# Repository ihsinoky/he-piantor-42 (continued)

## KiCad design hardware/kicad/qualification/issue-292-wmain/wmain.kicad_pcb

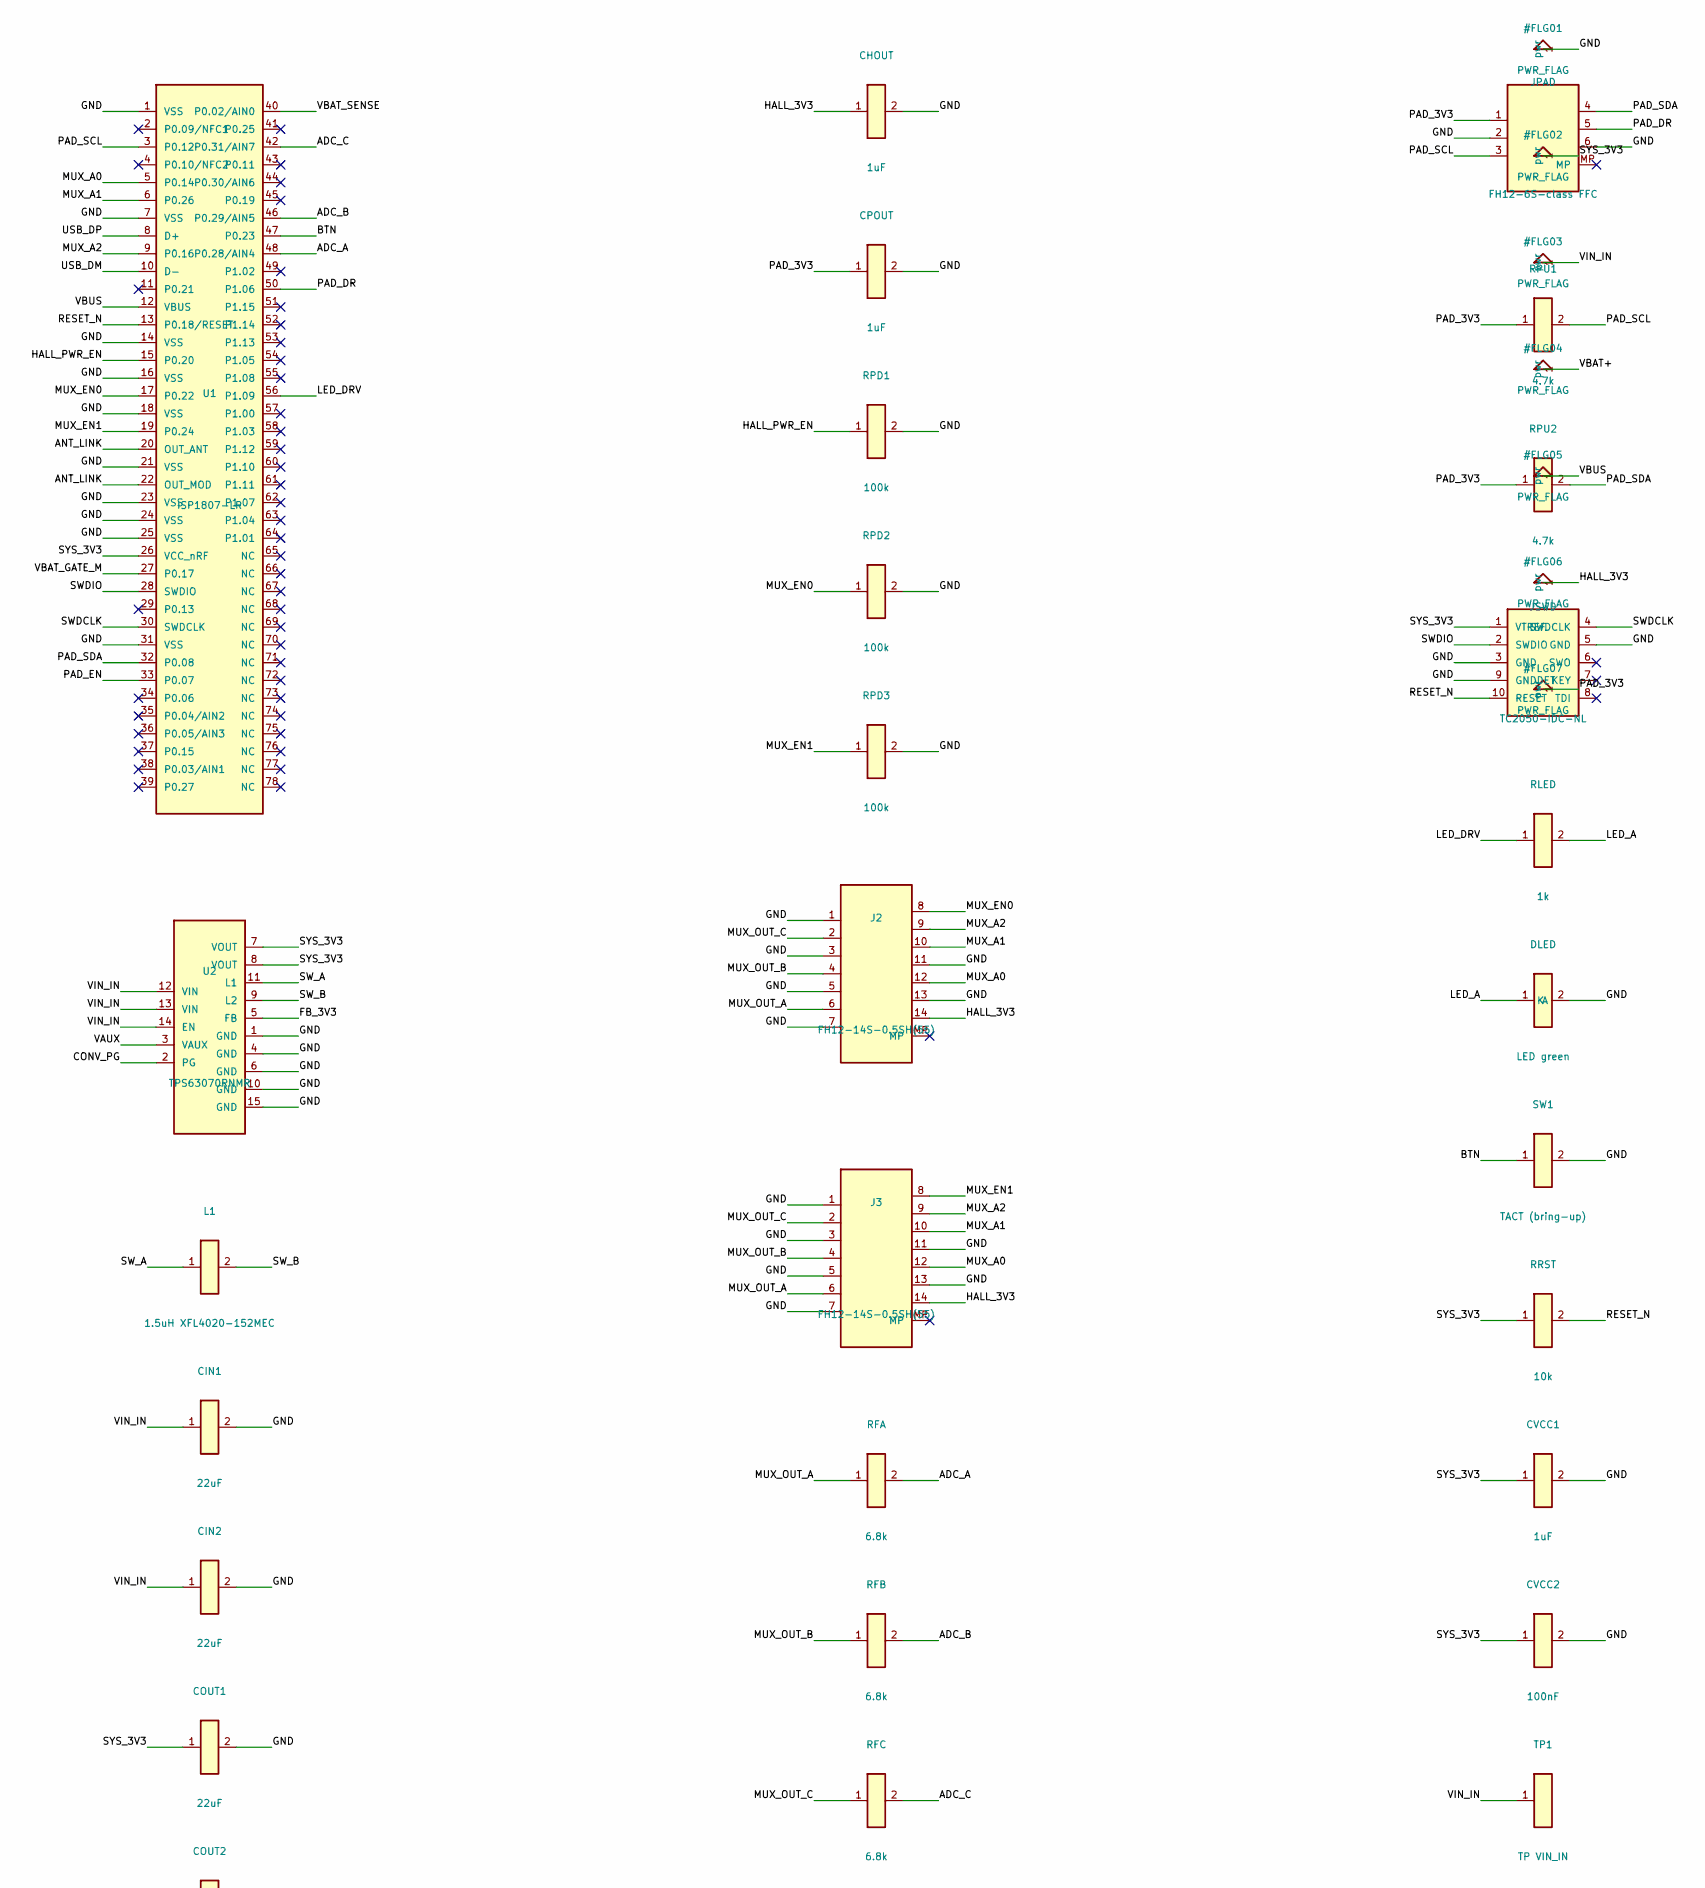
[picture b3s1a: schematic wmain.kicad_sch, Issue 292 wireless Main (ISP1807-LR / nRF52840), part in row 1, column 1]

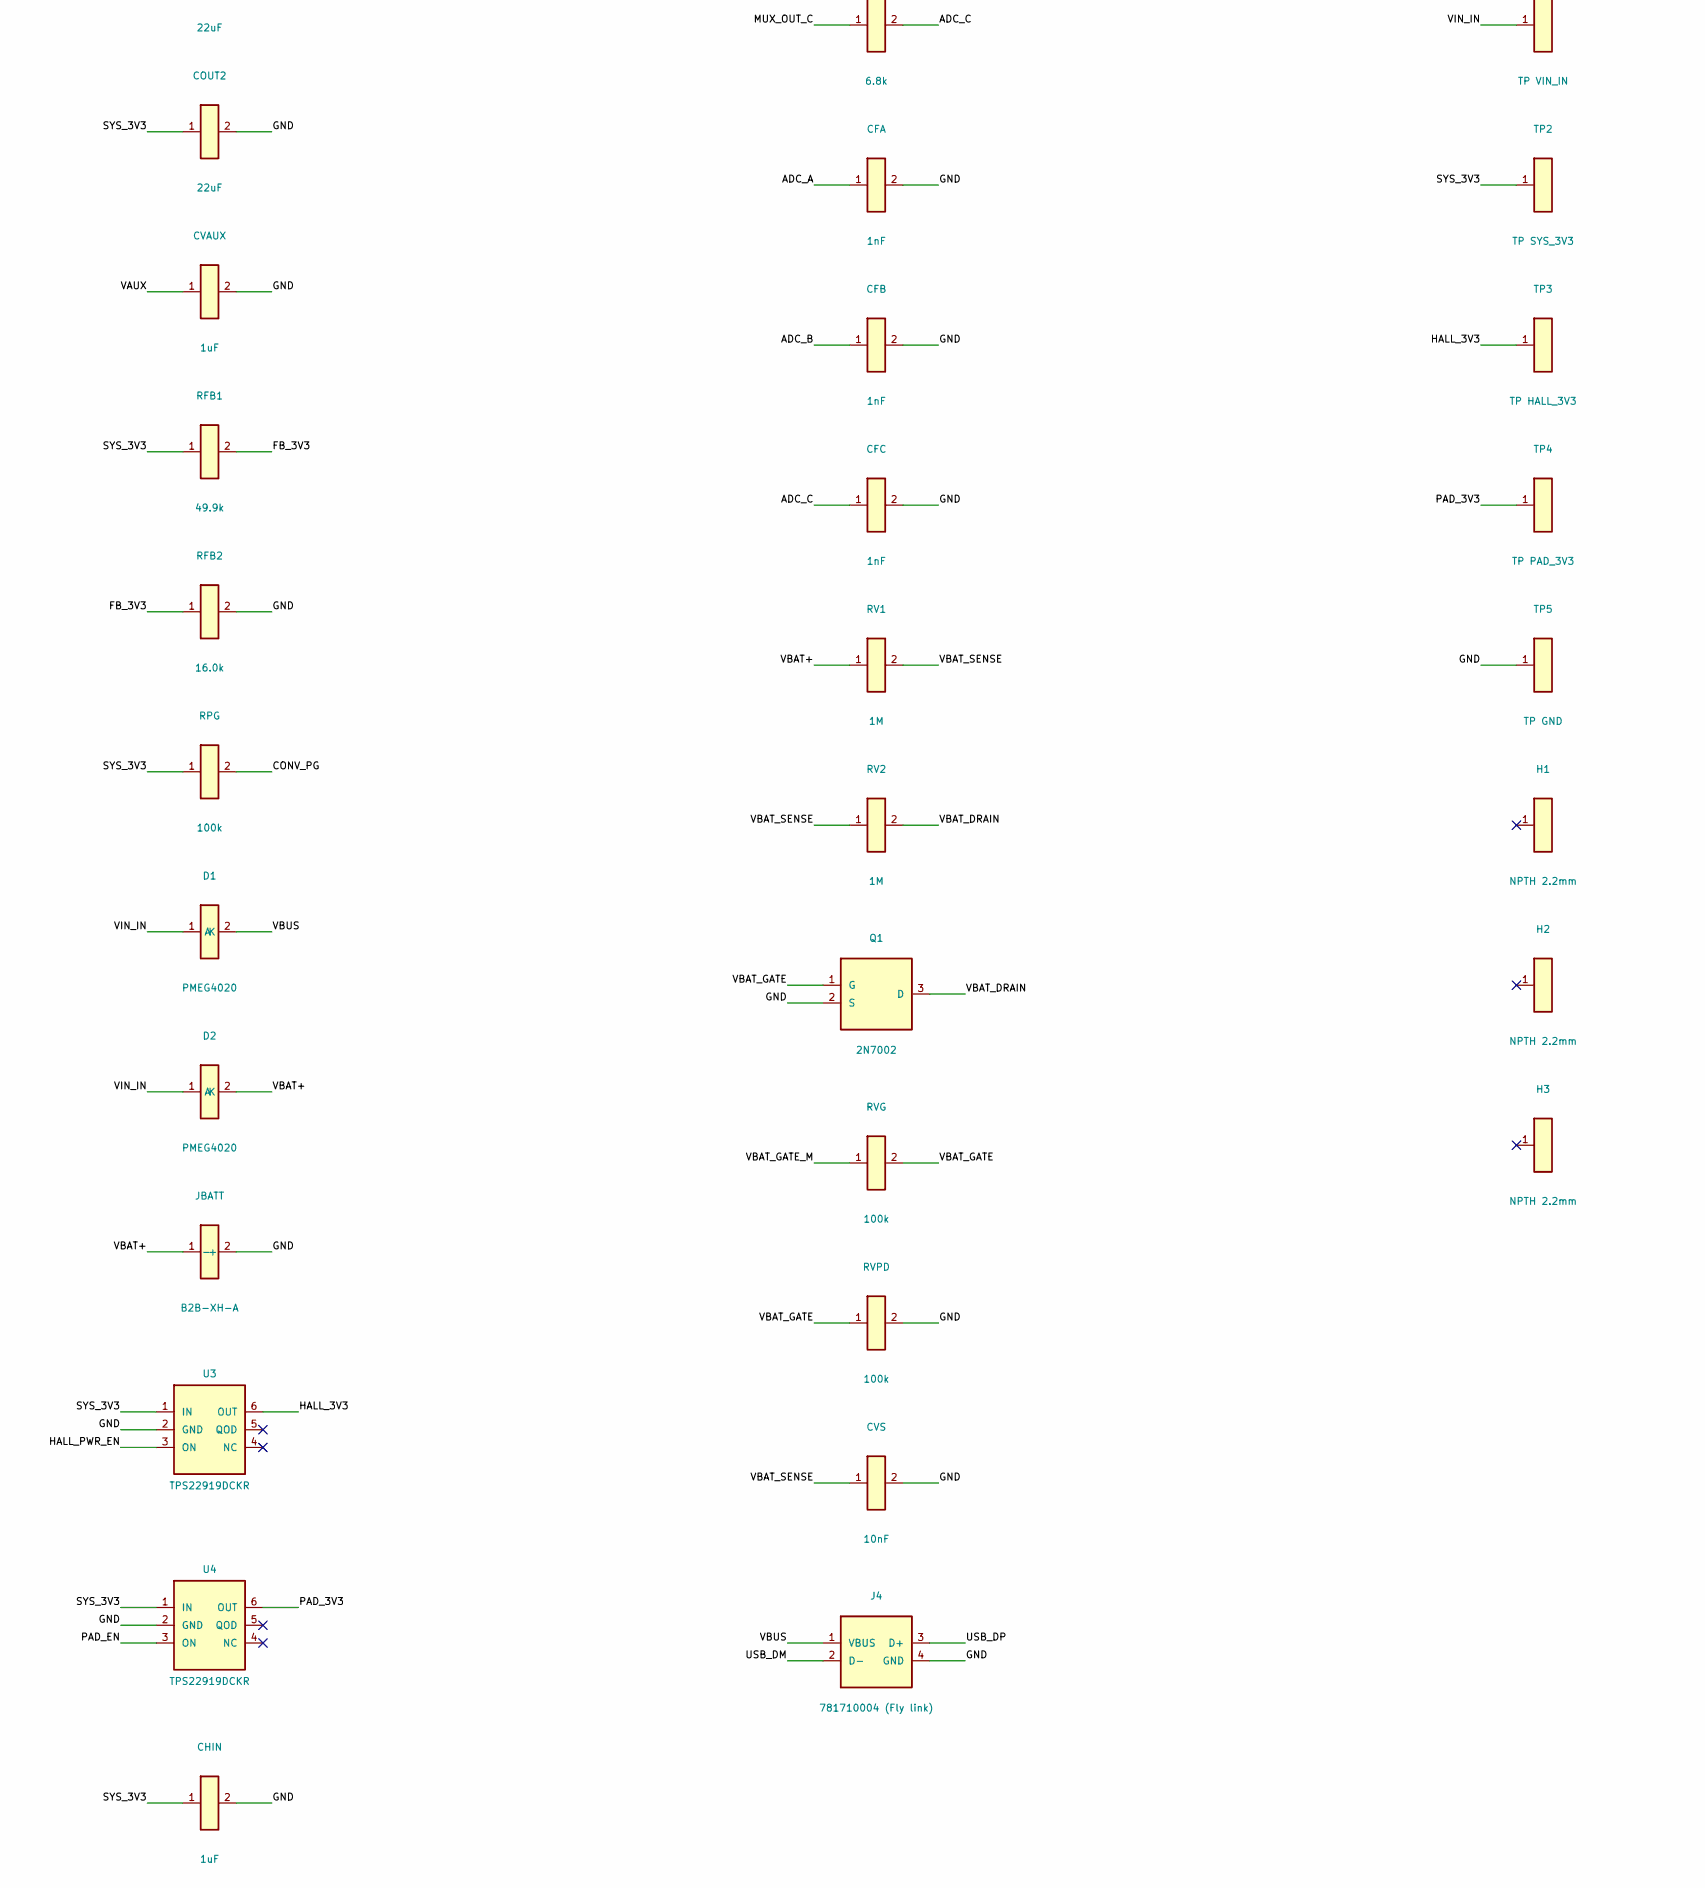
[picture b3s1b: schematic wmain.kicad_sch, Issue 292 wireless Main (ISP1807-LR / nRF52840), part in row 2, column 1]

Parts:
CFA: 1nF; C_0603
CFB: 1nF; C_0603
CFC: 1nF; C_0603
CHIN: 1uF; C_0603
CHOUT: 1uF; C_0603
CIN1, CIN2: 22uF; C_0805
COUT1, COUT2: 22uF; C_0805
CPOUT: 1uF; C_0603
CVAUX: 1uF; C_0603
CVCC1: 1uF; C_0603
CVCC2: 100nF; C_0603
CVS: 10nF; C_0603
D1, D2: PMEG4020; SOD-123
DLED: LED green; R_0603
H1, H2, H3: NPTH 2.2mm; MountingHole_2.2mm
J2, J3: FH12-14S-0.5SH(55); FH12-14S-0.5SH
J4: 781710004 (Fly link); Pico-EZmate_781710004
JBATT: B2B-XH-A; GH2
JPAD: FH12-6S-class FFC; FFC6_0.5mm_land
JSWD: TC2050-IDC-NL
L1: 1.5uH XFL4020-152MEC; XFL4020
Q1: 2N7002; SOT-23
RFA: 6.8k; R_0603
RFB: 6.8k; R_0603
RFB1: 49.9k; R_0603
RFB2: 16.0k; R_0603
RFC: 6.8k; R_0603
RLED: 1k; R_0603
RPD1, RPD2, RPD3: 100k; R_0603
RPG: 100k; R_0603
RPU1, RPU2: 4.7k; R_0603
RRST: 10k; R_0603
RV1, RV2: 1M; R_0603
RVG: 100k; R_0603
RVPD: 100k; R_0603
SW1: TACT (bring-up); TACT_2pad
TP1: TP VIN_IN; TestPoint
TP2: TP SYS_3V3; TestPoint
TP3: TP HALL_3V3; TestPoint
TP4: TP PAD_3V3; TestPoint
TP5: TP GND; TestPoint
U1: ISP1807-LR
U2: TPS63070RNMR
U3, U4: TPS22919DCKR

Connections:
ADC_A: CFA.1, RFA.2, U1.48 (P0.28/AIN4)
ADC_B: CFB.1, RFB.2, U1.46 (P0.29/AIN5)
ADC_C: CFC.1, RFC.2, U1.42 (P0.31/AIN7)
ANT_LINK: U1.20 (OUT_ANT), U1.22 (OUT_MOD)
BTN: SW1.1, U1.47 (P0.23)
CONV_PG: RPG.2, U2.2 (PG)
FB_3V3: RFB1.2, RFB2.1, U2.5 (FB)
GND: CFA.2, CFB.2, CFC.2, CHIN.2, CHOUT.2, CIN1.2, CIN2.2, COUT1.2, COUT2.2, CPOUT.2, CVAUX.2, CVCC1.2, CVCC2.2, CVS.2, DLED.2 (K), J2.1, J2.3, J2.5, J2.7, J2.11, J2.13, J3.1, J3.3, J3.5, J3.7, J3.11, J3.13, J4.4 (GND), JBATT.2 (-), JPAD.2, JPAD.6, JSWD.3 (GND), JSWD.5 (GND), JSWD.9 (GNDDET), Q1.2 (S), RFB2.2, RPD1.2, RPD2.2, RPD3.2, RVPD.2, SW1.2, TP5.1, U1.1 (VSS), U1.7 (VSS), U1.14 (VSS), U1.16 (VSS), U1.18 (VSS), U1.21 (VSS), U1.23 (VSS), U1.24 (VSS), U1.25 (VSS), U1.31 (VSS), U2.1 (GND), U2.4 (GND), U2.6 (GND), U2.10 (GND), U2.15 (GND), U3.2 (GND), U4.2 (GND)
HALL_3V3: CHOUT.1, J2.14, J3.14, TP3.1, U3.6 (OUT)
HALL_PWR_EN: RPD1.1, U1.15 (P0.20), U3.3 (ON)
LED_A: DLED.1 (A), RLED.2
LED_DRV: RLED.1, U1.56 (P1.09)
MUX_A0: J2.12, J3.12, U1.5 (P0.14)
MUX_A1: J2.10, J3.10, U1.6 (P0.26)
MUX_A2: J2.9, J3.9, U1.9 (P0.16)
MUX_EN0: J2.8, RPD2.1, U1.17 (P0.22)
MUX_EN1: J3.8, RPD3.1, U1.19 (P0.24)
MUX_OUT_A: J2.6, J3.6, RFA.1
MUX_OUT_B: J2.4, J3.4, RFB.1
MUX_OUT_C: J2.2, J3.2, RFC.1
PAD_3V3: CPOUT.1, JPAD.1, RPU1.1, RPU2.1, TP4.1, U4.6 (OUT)
PAD_DR: JPAD.5, U1.50 (P1.06)
PAD_EN: U1.33 (P0.07), U4.3 (ON)
PAD_SCL: JPAD.3, RPU1.2, U1.3 (P0.12)
PAD_SDA: JPAD.4, RPU2.2, U1.32 (P0.08)
RESET_N: JSWD.10 (RESET), RRST.2, U1.13 (P0.18/RESET)
SWDCLK: JSWD.4 (SWDCLK), U1.30 (SWDCLK)
SWDIO: JSWD.2 (SWDIO), U1.28 (SWDIO)
SW_A: L1.1, U2.11 (L1)
SW_B: L1.2, U2.9 (L2)
SYS_3V3: CHIN.1, COUT1.1, COUT2.1, CVCC1.1, CVCC2.1, JSWD.1 (VTREF), RFB1.1, RPG.1, RRST.1, TP2.1, U1.26 (VCC_nRF), U2.7 (VOUT), U2.8 (VOUT), U3.1 (IN), U4.1 (IN)
USB_DM: J4.2 (D-), U1.10 (D-)
USB_DP: J4.3 (D+), U1.8 (D+)
VAUX: CVAUX.1, U2.3 (VAUX)
VBAT+: D2.2 (A), JBATT.1 (+), RV1.1
VBAT_DRAIN: Q1.3 (D), RV2.2
VBAT_GATE: Q1.1 (G), RVG.2, RVPD.1
VBAT_GATE_M: RVG.1, U1.27 (P0.17)
VBAT_SENSE: CVS.1, RV1.2, RV2.1, U1.40 (P0.02/AIN0)
VBUS: D1.2 (A), J4.1 (VBUS), U1.12 (VBUS)
VIN_IN: CIN1.1, CIN2.1, D1.1 (K), D2.1 (K), TP1.1, U2.12 (VIN), U2.13 (VIN), U2.14 (EN)

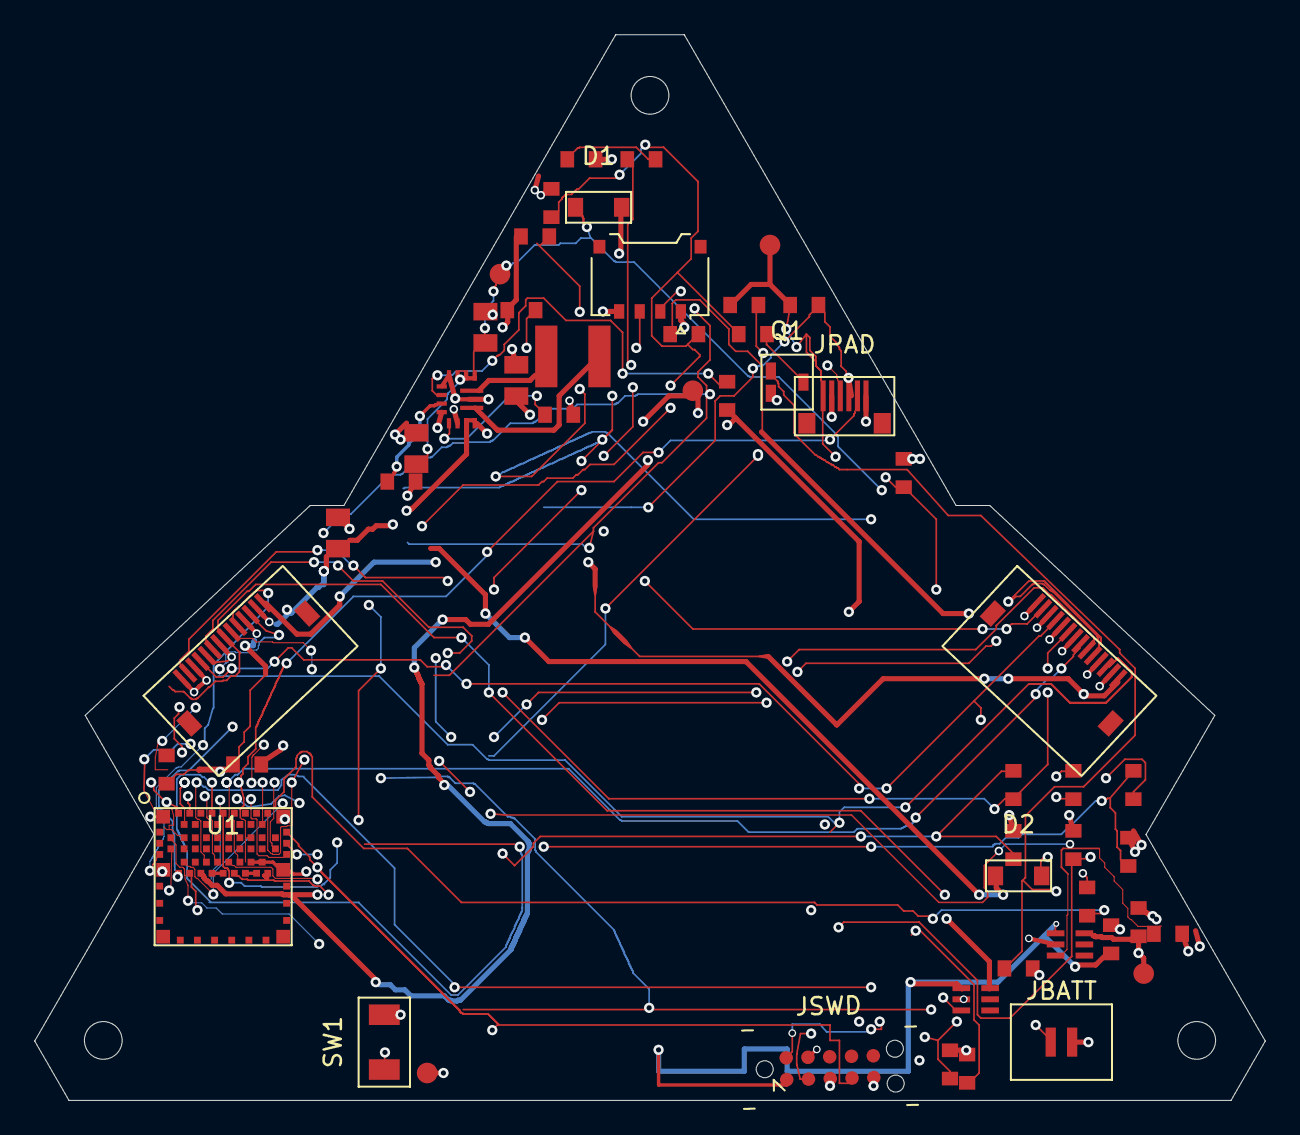
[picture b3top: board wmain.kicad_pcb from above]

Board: 4 copper layers, 71.8 x 62.2 mm, 55 parts (0 on the bottom side), 41 nets.

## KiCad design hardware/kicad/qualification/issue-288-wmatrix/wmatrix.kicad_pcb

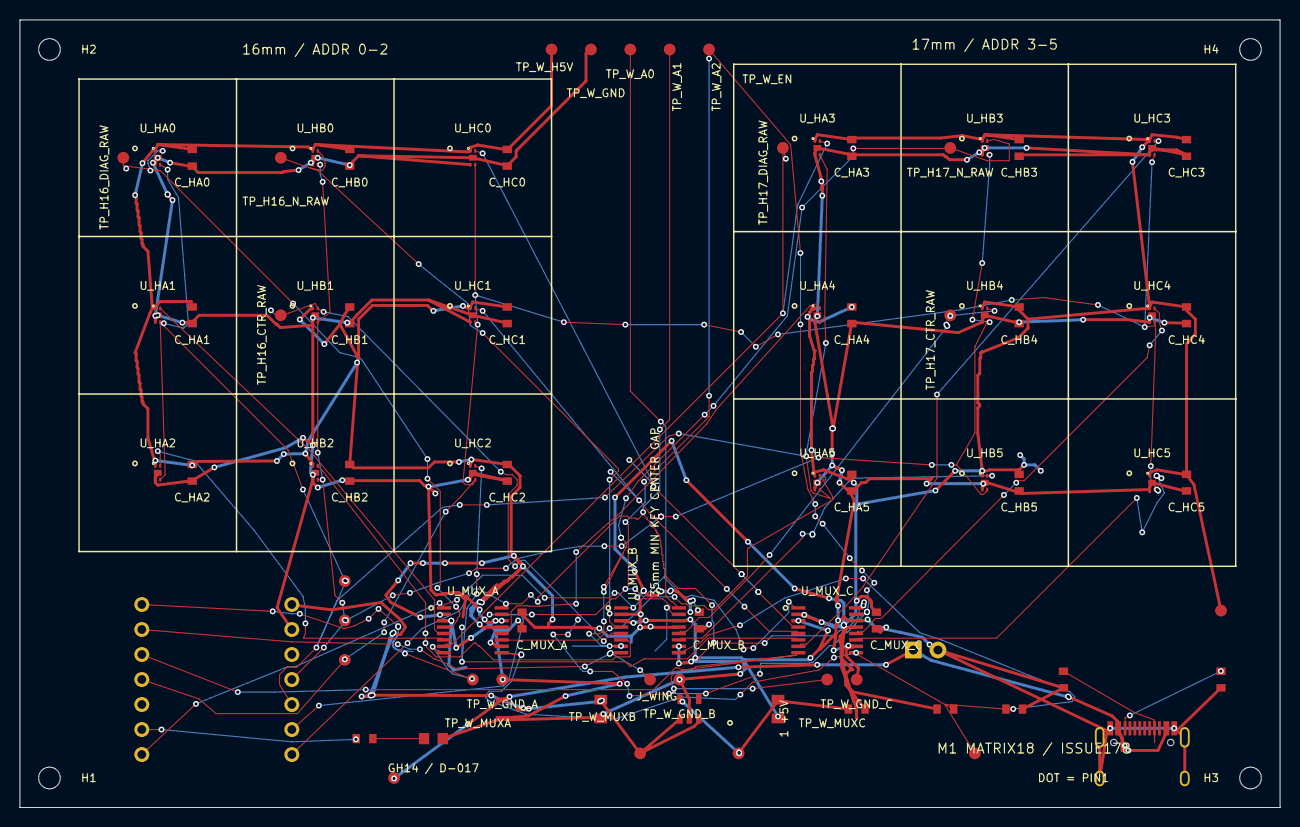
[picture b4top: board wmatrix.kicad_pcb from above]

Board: 2 copper layers, 128.0 x 80.0 mm, 85 parts (0 on the bottom side), 37 nets.

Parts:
C_HA0, C_HA1, C_HA2, C_HA3, C_HA4, C_HA5: GRM188R71C104KA01D; capacitor
C_HB0, C_HB1, C_HB2, C_HB3, C_HB4, C_HB5: GRM188R71C104KA01D; capacitor
C_HC0, C_HC1, C_HC2, C_HC3, C_HC4, C_HC5: GRM188R71C104KA01D; capacitor
C_LDO_IN: 10uF; C_0805
C_LDO_OUT: 10uF; C_0805
C_MUX_A: GRM188R71C104KA01D; capacitor
C_MUX_B: GRM188R71C104KA01D; capacitor
C_MUX_C: GRM188R71C104KA01D; capacitor
D_LED: KT-0805G green; LED_0805
H1, H2, H3, H4: NPTH_2.2mm; mounting
J_BATT: B2B-XH-A; JST_XH_B2B-XH-A_1x02
J_USB: TYPE-C-31-M-12
Q_PROT: AO3401A; AO3401A_SOT-23
R_CC1, R_CC2: 5.1k; R_0603
R_DIV1, R_DIV2: 10k; R_0603
R_LED: 1k; R_0603
R_SHUNT: 0R (current-shunt position); R_0603
TP_3V3_SRC: TestPoint; TP_1.2mm
TP_A0, TP_A1, TP_A2: PCB_PAD_1.2MM; testpoint
TP_EN_A: TestPoint; TP_1.2mm
TP_EN_B: TestPoint; TP_1.2mm
TP_EN_C: TestPoint; TP_1.2mm
TP_GND_A: PCB_PAD_1.2MM; testpoint
TP_GND_B: PCB_PAD_1.2MM; testpoint
TP_GND_C: PCB_PAD_1.2MM; testpoint
TP_GND_D: PCB_PAD_1.2MM; testpoint
TP_H16_CTR, TP_H16_DIAG, TP_H16_N, TP_H17_CTR, TP_H17_DIAG, TP_H17_N: PCB_PAD_1.2MM; testpoint
TP_MUXA: PCB_PAD_1.2MM; testpoint
TP_MUXB: PCB_PAD_1.2MM; testpoint
TP_MUXC: PCB_PAD_1.2MM; testpoint
TP_RAIL_E: TestPoint; TP_1.2mm
TP_RAIL_N: PCB_PAD_1.2MM; testpoint
TP_REF: TestPoint; TP_1.2mm
TP_VIN: TestPoint; TP_1.2mm
TP_VIN_SRC: TestPoint; TP_1.2mm
U_HA0, U_HA1, U_HA2, U_HA3, U_HA4, U_HA5: TMAG5253BA3IQDMRR; TMAG5253BA3_X2SON-4
U_HB0, U_HB1, U_HB2, U_HB3, U_HB4, U_HB5: TMAG5253BA3IQDMRR; TMAG5253BA3_X2SON-4
U_HC0, U_HC1, U_HC2, U_HC3, U_HC4, U_HC5: TMAG5253BA3IQDMRR; TMAG5253BA3_X2SON-4
U_LDO: AP2112K-3.3TRG1; AP2112_SOT-23-5
U_MUXA: TMUX1208PWR; mux
U_MUXB: TMUX1208PWR; mux
U_MUXC: TMUX1208PWR; mux
U_XIAO: XIAO nRF52840 (socket, hand-fit); XIAO_nRF52840_SOCKET

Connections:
CC1: J_USB.3, R_CC1.1
CC2: J_USB.10, R_CC2.1
EN_A: TP_EN_A.1, U_HA0.3, U_HA1.3, U_HA2.3, U_HA3.3, U_HA4.3, U_HA5.3, U_XIAO.10
EN_B: TP_EN_B.1, U_HB0.3, U_HB1.3, U_HB2.3, U_HB3.3, U_HB4.3, U_HB5.3, U_XIAO.11
EN_C: TP_EN_C.1, U_HC0.3, U_HC1.3, U_HC2.3, U_HC3.3, U_HC4.3, U_HC5.3, U_XIAO.4
GND: C_HA0.2, C_HA1.2, C_HA2.2, C_HA3.2, C_HA4.2, C_HA5.2, C_HB0.2, C_HB1.2, C_HB2.2, C_HB3.2, C_HB4.2, C_HB5.2, C_HC0.2, C_HC1.2, C_HC2.2, C_HC3.2, C_HC4.2, C_HC5.2, C_LDO_IN.2, C_LDO_OUT.2, C_MUX_A.2, C_MUX_B.2, C_MUX_C.2, D_LED.2, J_BATT.2, J_USB.1, J_USB.12, J_USB.13, Q_PROT.1, R_CC1.2, R_CC2.2, R_DIV2.2, TP_GND_A.1, TP_GND_B.1, TP_GND_C.1, TP_GND_D.1, U_HA0.2, U_HA0.5, U_HA1.2, U_HA1.5, U_HA2.2, U_HA2.5, U_HA3.2, U_HA3.5, U_HA4.2, U_HA4.5, U_HA5.2, U_HA5.5, U_HB0.2, U_HB0.5, U_HB1.2, U_HB1.5, U_HB2.2, U_HB2.5, U_HB3.2, U_HB3.5, U_HB4.2, U_HB4.5, U_HB5.2, U_HB5.5, U_HC0.2, U_HC0.5, U_HC1.2, U_HC1.5, U_HC2.2, U_HC2.5, U_HC3.2, U_HC3.5, U_HC4.2, U_HC4.5, U_HC5.2, U_HC5.5, U_LDO.2, U_MUXA.3, U_MUXA.10, U_MUXA.14, U_MUXB.3, U_MUXB.10, U_MUXB.14, U_MUXC.3, U_MUXC.10, U_MUXC.14, U_XIAO.13
HALL_3V3: C_HA0.1, C_HA1.1, C_HA2.1, C_HA3.1, C_HA4.1, C_HA5.1, C_HB0.1, C_HB1.1, C_HB2.1, C_HB3.1, C_HB4.1, C_HB5.1, C_HC0.1, C_HC1.1, C_HC2.1, C_HC3.1, C_HC4.1, C_HC5.1, C_MUX_A.1, C_MUX_B.1, C_MUX_C.1, R_DIV1.1, R_SHUNT.2, TP_RAIL_E.1, TP_RAIL_N.1, U_HA0.1, U_HA1.1, U_HA2.1, U_HA3.1, U_HA4.1, U_HA5.1, U_HB0.1, U_HB1.1, U_HB2.1, U_HB3.1, U_HB4.1, U_HB5.1, U_HC0.1, U_HC1.1, U_HC2.1, U_HC3.1, U_HC4.1, U_HC5.1, U_MUXA.2, U_MUXA.13, U_MUXB.2, U_MUXB.13, U_MUXC.2, U_MUXC.13
HALL_3V3_SRC: C_LDO_OUT.1, R_SHUNT.1, TP_3V3_SRC.1, U_LDO.5
H_A0_RAW: TP_H16_DIAG.1, U_HA0.4, U_MUXA.4
H_A1_RAW: U_HA1.4, U_MUXA.5
H_A2_RAW: U_HA2.4, U_MUXA.6
H_A3_RAW: TP_H17_DIAG.1, U_HA3.4, U_MUXA.7
H_A4_RAW: U_HA4.4, U_MUXA.12
H_A5_RAW: U_HA5.4, U_MUXA.11
H_B0_RAW: TP_H16_N.1, U_HB0.4, U_MUXB.4
H_B1_RAW: TP_H16_CTR.1, U_HB1.4, U_MUXB.5
H_B2_RAW: U_HB2.4, U_MUXB.6
H_B3_RAW: TP_H17_N.1, U_HB3.4, U_MUXB.7
H_B4_RAW: TP_H17_CTR.1, U_HB4.4, U_MUXB.12
H_B5_RAW: U_HB5.4, U_MUXB.11
H_C0_RAW: U_HC0.4, U_MUXC.4
H_C1_RAW: U_HC1.4, U_MUXC.5
H_C2_RAW: U_HC2.4, U_MUXC.6
H_C3_RAW: U_HC3.4, U_MUXC.7
H_C4_RAW: U_HC4.4, U_MUXC.12
H_C5_RAW: U_HC5.4, U_MUXC.11
LED_A: D_LED.1, R_LED.2
LED_DRV: R_LED.1, U_XIAO.6
MUXA_OUT: TP_MUXA.1, U_MUXA.8, U_XIAO.1
MUXB_OUT: TP_MUXB.1, U_MUXB.8, U_XIAO.2
MUXC_OUT: TP_MUXC.1, U_MUXC.8, U_XIAO.3
MUX_A0: TP_A0.1, U_MUXA.1, U_MUXB.1, U_MUXC.1, U_XIAO.7
MUX_A1: TP_A1.1, U_MUXA.16, U_MUXB.16, U_MUXC.16, U_XIAO.8
MUX_A2: TP_A2.1, U_MUXA.15, U_MUXB.15, U_MUXC.15, U_XIAO.9
REF_RAIL: R_DIV1.2, R_DIV2.1, TP_REF.1, U_MUXA.9, U_MUXB.9, U_MUXC.9
VIN: C_LDO_IN.1, Q_PROT.3, TP_VIN.1, U_LDO.1, U_LDO.3, U_XIAO.14
VIN_SRC: J_BATT.1, J_USB.2, J_USB.11, Q_PROT.2, TP_VIN_SRC.1

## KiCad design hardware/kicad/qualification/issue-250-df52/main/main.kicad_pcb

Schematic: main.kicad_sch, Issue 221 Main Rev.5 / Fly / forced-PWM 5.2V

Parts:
C1: 15pF; C1
C2: 15pF; C2
C3: 100nF; C3
C4: 100nF; C4
C5: 100nF; C5
C6: 100nF; C6
C7: 100nF; C7
C8: 100nF; C8
C9: 100nF; C9
C10: 100nF; C10
C11: 100nF; C11
C12: 1uF; C12
C13: 1uF; C13
C14: 10uF; C14
C15: 100nF; C15
C16: 1uF; C16
C17: 1uF; C17
C18: 1uF; C18
C19: 1uF; C19
C20: 1nF; C20
C21: 1nF; C21
C22: 1nF; C22
C23: 22uF 16V X6S 0805; C23
C24: 22uF 16V X6S 0805; C24
C25: 100nF; C25
C26: 22uF 16V X7R 1210; C26
C27: 22uF 16V X7R 1210; C27
C28: 22uF 16V X7R 1210; C28
H1: NPTH_2.2mm; H1
H2: NPTH_2.2mm; H2
H3: NPTH_2.2mm; H3
J2, J3: DF52-14S-0.8H(21); DF52-14S-0.8H_14
J4: 781710004; J4
L1: 1.5uH XFL4020-152MEC; L1
R3: 27; R3
R4: 27; R4
R5: 1k; R5
R6: 100k; R6
R7: 100k; R7
R8: 10k; R8
R9: 1k; R9
R10: 6.8k; R10
R11: 10k; R11
R12: 6.8k; R12
R13: 10k; R13
R14: 6.8k; R14
R15: 10k; R15
R16: 100k; R16
R17: 54.9k 0.1% 25ppm/K; R17
R18: 10k 0.1% 25ppm/K; R18
R19: 100k; R19
TP1: TestPoint; TP1
TP2: TestPoint; TP2
TP3: TestPoint; TP3
TP4: TestPoint; TP4
U1: RP2040; U1
U3: W25Q16JVUXIQ; U3
U4: AP2112K-3.3TRG1; U4
U5: TPS22919DCKR; U5
U6: TPS63070RNMR; U6
Y1: ABM8-272-T3; Y1

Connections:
ADC_A: C20.1, R10.2, R11.1, U1.38 (GPIO26/ADC0)
ADC_B: C21.1, R12.2, R13.1, U1.39 (GPIO27/ADC1)
ADC_C: C22.1, R14.2, R15.1, U1.40 (GPIO28/ADC2)
FB_5V2: R17.2, R18.1, U6.5 (FB)
GND: C1.2, C2.2, C3.2, C4.2, C5.2, C6.2, C7.2, C8.2, C9.2, C10.2, C11.2, C12.2, C13.2, C14.2, C15.2, C16.2, C17.2, C18.2, C19.2, C20.2, C21.2, C22.2, C23.2, C24.2, C25.2, C26.2, C27.2, C28.2, J2.2, J2.4, J2.8, J2.10, J2.12, J2.14, J3.2, J3.4, J3.8, J3.10, J3.12, J3.14, J4.4, R6.2, R7.2, R11.2, R13.2, R15.2, R16.2, R18.2, U1.19 (TESTEN), U1.57 (GND), U3.4 (GND), U4.2 (GND), U5.2 (GND), U6.1 (PS/SYNC), U6.4 (GND), U6.6 (FB2), U6.10 (PGND), U6.15 (VSEL), Y1.2 (G), Y1.4 (G)
HALL_5V: C19.1, J2.1, J3.1, U5.6 (OUT)
HALL_PWR_EN: R7.1, U1.9 (GPIO7), U5.3 (ON), U6.14 (EN)
MUX_A0: J2.3, J3.3, U1.4 (GPIO2)
MUX_A1: J2.5, J3.5, U1.5 (GPIO3)
MUX_A2: J2.6, J3.6, U1.6 (GPIO4)
MUX_EN1: J3.7, R16.1, U1.8 (GPIO6)
MUX_OUT_A: J2.9, J3.9, R10.1
MUX_OUT_B: J2.11, J3.11, R12.1
MUX_OUT_C: J2.13, J3.13, R14.1
QSPI_SCLK: U1.52 (QSPI_SCLK), U3.6 (CLK)
QSPI_SD0: U1.53 (QSPI_SD0), U3.5 (DI(IO0))
QSPI_SD1: U1.55 (QSPI_SD1), U3.2 (DO(IO1))
QSPI_SD2: U1.54 (QSPI_SD2), U3.3 (~WP(IO2))
QSPI_SD3: U1.51 (QSPI_SD3), U3.7 (~HOLD(IO3))
QSPI_SS_FLASH: R5.2, TP4.1, U3.1 (~CS)
QSPI_SS_MCU: R5.1, U1.56 (~QSPI_SS)
RAIL_PG: R19.2, U6.2 (PG)
RUN: R8.2, TP3.1, U1.26 (RUN)
SW1: L1.1, U6.11 (L1)
SW2: L1.2, U6.9 (L2)
SWCLK: TP2.1, U1.24 (SWCLK)
SWDIO: TP1.1, U1.25 (SWDIO)
USB_DM: R4.2, U1.46 (USB_DM)
USB_DM_ESD: J4.2, R4.1
USB_DP: R3.2, U1.47 (USB_DP)
USB_DP_ESD: J4.3, R3.1
V1V1: C11.1, C13.1, U1.23 (DVDD), U1.45 (VREG_VOUT), U1.50 (DVDD)
V3V3: C3.1, C4.1, C5.1, C6.1, C7.1, C8.1, C9.1, C10.1, C12.1, C14.1, C15.1, C17.1, R8.1, R19.1, U1.1 (IOVDD), U1.10 (IOVDD), U1.22 (IOVDD), U1.33 (IOVDD), U1.42 (IOVDD), U1.43 (ADC_AVDD), U1.44 (VREG_VIN), U1.48 (USB_VDD), U1.49 (IOVDD), U3.8 (VCC), U4.5 (VOUT)
V5V2: C26.1, C27.1, C28.1, R17.1, U5.1 (IN), U6.7 (VOUT), U6.8 (VOUT)
VAUX: C25.1, U6.3 (VAUX)
VBUS: C16.1, C18.1, C23.1, C24.1, J4.1, U4.1 (VIN), U4.3 (EN), U6.12 (VIN), U6.13 (VIN)
WING_EN: J2.7, R6.1, U1.7 (GPIO5)
XIN: C1.1, U1.20 (XIN), Y1.1
XOUT: R9.2, U1.21 (XOUT)
XOUT_XTAL: C2.1, R9.1, Y1.3

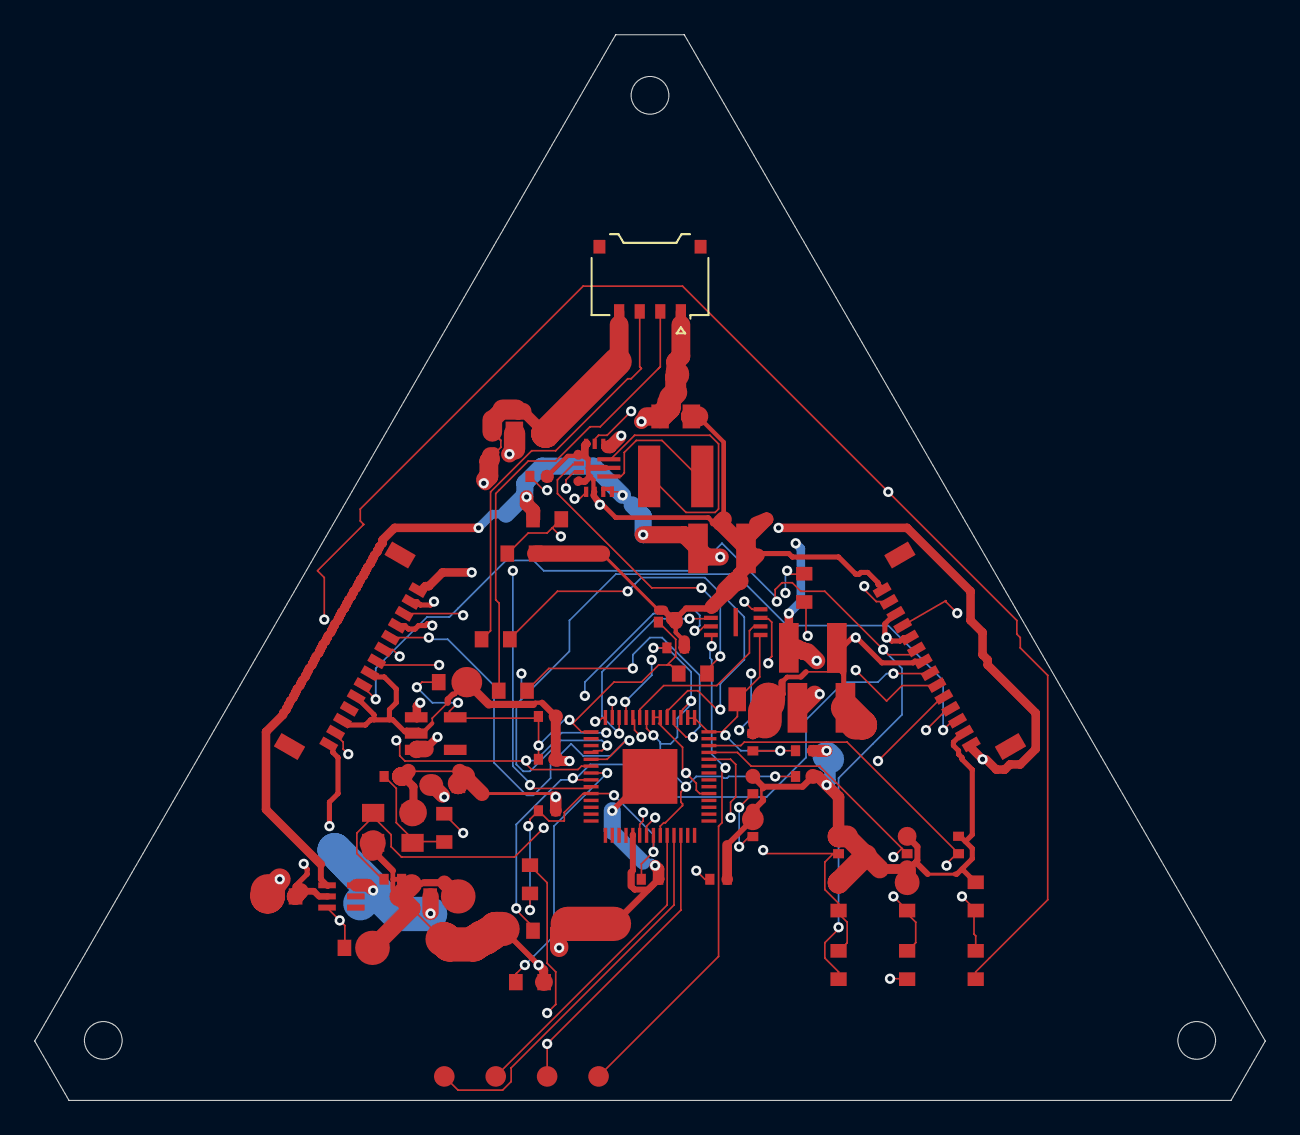
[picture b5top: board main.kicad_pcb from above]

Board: 4 copper layers, 71.8 x 62.2 mm, 62 parts (0 on the bottom side), 40 nets.

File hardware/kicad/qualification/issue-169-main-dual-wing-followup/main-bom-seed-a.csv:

ref,value,footprint,part_number,lcsc,assembled,source,procurement_confirmed
C1,15pF,Stage169:C1,0402CG150J500NT,C1548,True,Inherited #124 ledger,False
C10,100nF,Stage169:C10,CL05B104KO5NNNC,C1525,True,Inherited #124 ledger,False
C11,100nF,Stage169:C11,CL05B104KO5NNNC,C1525,True,Inherited #124 ledger,False
C12,1uF,Stage169:C12,CL05A105KA5NQNC,C52923,True,Inherited #124 ledger,False
C13,1uF,Stage169:C13,CL05A105KA5NQNC,C52923,True,Inherited #124 ledger,False
C14,10uF,Stage169:C14,CL21A106KAYNNNE,C15850,True,Inherited #124 ledger,False
C15,100nF,Stage169:C15,CL05B104KO5NNNC,C1525,True,Inherited #124 ledger,False
C16,1uF,Stage169:C16,CL10A105KB8NNNC,C15849,True,Inherited #124 ledger,False
C17,1uF,Stage169:C17,CL10A105KB8NNNC,C15849,True,Inherited #124 ledger,False
C18,1uF,Stage169:C18,CL10A105KB8NNNC,C15849,True,Inherited #124 ledger,False
C19,1uF,Stage169:C19,CL10A105KB8NNNC,C15849,True,Inherited #124 ledger,False
C2,15pF,Stage169:C2,0402CG150J500NT,C1548,True,Inherited #124 ledger,False
C20,1nF,Stage169:C20,0402B102K500NT,C1523,True,Inherited #124 ledger,False
C21,1nF,Stage169:C21,0402B102K500NT,C1523,True,Inherited #124 ledger,False
C22,1nF,Stage169:C22,0402B102K500NT,C1523,True,Inherited #124 ledger,False
C23,22uF 16V X6S 0805,Stage169:C23,GRM21BC81C226ME44L,C258782,True,Issue169 selected exact MPN; sourcing and manufacturer acceptance pending,False
C24,22uF 16V X6S 0805,Stage169:C24,GRM21BC81C226ME44L,C258782,True,Issue169 selected exact MPN; sourcing and manufacturer acceptance pending,False
C25,100nF,Stage169:C25,GRM155R71E104KE14D,C77014,True,Issue169 selected exact MPN; sourcing and manufacturer acceptance pending,False
C26,22uF 16V X6S 0805,Stage169:C26,GRM21BC81C226ME44L,C258782,True,Issue169 selected exact MPN; sourcing and manufacturer acceptance pending,False
C27,22uF 16V X6S 0805,Stage169:C27,GRM21BC81C226ME44L,C258782,True,Issue169 selected exact MPN; sourcing and manufacturer acceptance pending,False
C28,22uF 16V X6S 0805,Stage169:C28,GRM21BC81C226ME44L,C258782,True,Issue169 selected exact MPN; sourcing and manufacturer acceptance pending,False
C3,100nF,Stage169:C3,CL05B104KO5NNNC,C1525,True,Inherited #124 ledger,False
C4,100nF,Stage169:C4,CL05B104KO5NNNC,C1525,True,Inherited #124 ledger,False
C5,100nF,Stage169:C5,CL05B104KO5NNNC,C1525,True,Inherited #124 ledger,False
C6,100nF,Stage169:C6,CL05B104KO5NNNC,C1525,True,Inherited #124 ledger,False
C7,100nF,Stage169:C7,CL05B104KO5NNNC,C1525,True,Inherited #124 ledger,False
C8,100nF,Stage169:C8,CL05B104KO5NNNC,C1525,True,Inherited #124 ledger,False
C9,100nF,Stage169:C9,CL05B104KO5NNNC,C1525,True,Inherited #124 ledger,False
J1,TYPE-C-31-M-12,Stage169:J1,TYPE-C-31-M-12,C165948,True,Inherited #124 ledger,False
J2,BM14B-GHS-TBT(LF)(SN),Stage169:J2,BM14B-GHS-TBT(LF)(SN),C265384,True,Inherited #124 ledger,False
J3,BM14B-GHS-TBT(LF)(SN),Stage169:J3,BM14B-GHS-TBT(LF)(SN),C265384,True,Issue169 selected exact MPN; sourcing and manufacturer acceptance pending,False
L1,1.5uH XFL4020-152MEC,Stage169:L1,XFL4020-152MEC,C3033018,True,Issue169 selected exact MPN; sourcing and manufacturer acceptance pending,False
R1,5.1k,Stage169:R1,0603WAF5101T5E,C23186,True,Inherited #124 ledger,False
R10,6.8k,Stage169:R10,0603WAF6801T5E,C23212,True,Inherited #124 ledger,False
R11,10k,Stage169:R11,0603WAF1002T5E,C25804,True,Inherited #124 ledger,False
R12,6.8k,Stage169:R12,0603WAF6801T5E,C23212,True,Inherited #124 ledger,False
R13,10k,Stage169:R13,0603WAF1002T5E,C25804,True,Inherited #124 ledger,False
R14,6.8k,Stage169:R14,0603WAF6801T5E,C23212,True,Inherited #124 ledger,False
R15,10k,Stage169:R15,0603WAF1002T5E,C25804,True,Inherited #124 ledger,False
R16,100k,Stage169:R16,0603WAF1003T5E,C25803,True,Issue169 selected exact MPN; sourcing and manufacturer acceptance pending,False
R17,54.9k 0.1% 25ppm/K,Stage169:R17,TNPW060354K9BEEA,,True,Issue169 selected exact MPN; sourcing and manufacturer acceptance pending,False
R18,10k 0.1% 25ppm/K,Stage169:R18,TNPW060310K0BEEA,C844890,True,Issue169 selected exact MPN; sourcing and manufacturer acceptance pending,False
R19,100k,Stage169:R19,0603WAF1003T5E,C25803,True,Issue169 selected exact MPN; sourcing and manufacturer acceptance pending,False
R2,5.1k,Stage169:R2,0603WAF5101T5E,C23186,True,Inherited #124 ledger,False
R3,27,Stage169:R3,0603WAF270JT5E,C25190,True,Inherited #124 ledger,False
R4,27,Stage169:R4,0603WAF270JT5E,C25190,True,Inherited #124 ledger,False
R5,1k,Stage169:R5,0603WAF1001T5E,C21190,True,Inherited #124 ledger,False
R6,100k,Stage169:R6,0603WAF1003T5E,C25803,True,Inherited #124 ledger,False
R7,100k,Stage169:R7,0603WAF1003T5E,C25803,True,Inherited #124 ledger,False
R8,10k,Stage169:R8,0603WAF1002T5E,C25804,True,Inherited #124 ledger,False
R9,1k,Stage169:R9,0603WAF1001T5E,C21190,True,Inherited #124 ledger,False
TP1,TestPoint,Stage169:TP1,N/A (bare PCB test pad),N/A,False,Inherited #124 ledger,False
TP2,TestPoint,Stage169:TP2,N/A (bare PCB test pad),N/A,False,Inherited #124 ledger,False
TP3,TestPoint,Stage169:TP3,N/A (bare PCB test pad),N/A,False,Inherited #124 ledger,False
TP4,TestPoint,Stage169:TP4,N/A (bare PCB test pad),N/A,False,Inherited #124 ledger,False
U1,RP2040,Stage169:U1,RP2040,C2040,True,Inherited #124 ledger,False
U2,USBLC6-2SC6,Stage169:U2,USBLC6-2SC6,C7519,True,Inherited #124 ledger,False
U3,W25Q16JVUXIQ,Stage169:U3,W25Q16JVUXIQ,C2843335,True,Inherited #124 ledger,False
U4,AP2112K-3.3TRG1,Stage169:U4,AP2112K-3.3TRG1,C51118,True,Inherited #124 ledger,False
U5,TPS22919DCKR,Stage169:U5,TPS22919DCKR,C2149796,True,Inherited #124 ledger,False
U6,TPS63070RNMR,Stage169:U6,TPS63070RNMR,C109322,True,Issue169 selected exact MPN; sourcing and manufacturer acceptance pending,False
Y1,ABM8-272-T3,Stage169:Y1,ABM8-272-T3,C20625731,True,Inherited #124 ledger,False
